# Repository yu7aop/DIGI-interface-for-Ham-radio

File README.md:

# DIGI-Interface
DIGI, PTT, CW interface, schematic, pcb, Eagle files

Project - Digi interface with 2 pots for input and output level of audio signal from PC.
Based on many different schematics, but adjusted to the needs of Radio club Zrenjanin YU7AOP.
This interface has proven to be good at working with different radio's (new and "old school":) such as:
FT901DM, FT101ZD, IC718, TS930S, FT950, FT897, some Codan's etc.

RS232 added as control port for CW and PTT. If not using CW or PTT line, simply set VOX on your RIG and use PTT via VOX on your radio.

Place interface into metal box to reduce RFI. I found on 2nd hand market defective 8 port LAN switch for about a 1$, perfect for this project.

PCB is toner-transfer method with hot Iron.
I have a lot of dual pots and PCB is adjusted for it. If you are friendly with Eagle you can change footprint for any other pot's.

Enjoy...

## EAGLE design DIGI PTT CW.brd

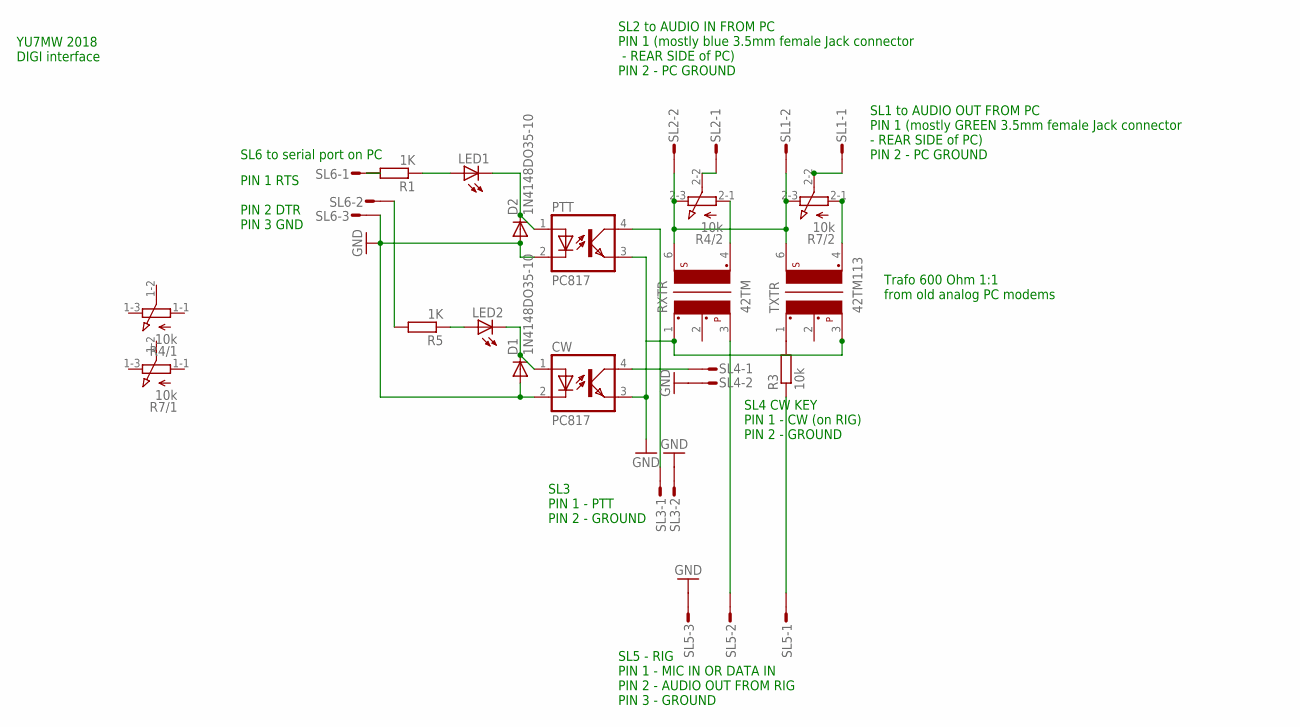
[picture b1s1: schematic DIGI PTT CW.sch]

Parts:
CW: PC817; DIL04
D1, D2: 1N4148DO35-10; DO35-10
LED1, LED2: LED3MM
PTT: PC817; DIL04
R1, R5: 1K; 0207/10
R3: 10k; 0207/10
R4, R7: 10k; 3RP/1610G
RXTR: 42TM
SL1, SL2, SL3, SL4: M02S; 02P
SL5, SL6: M03S; 03P
TXTR: 42TM113; 42TM

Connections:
GND: CW.2 (C), CW.3 (EMIT), D1.A, D2.A, PTT.2 (C), PTT.3 (EMIT), RXTR.1, SL3.2, SL4.2, SL5.3, SL6.3, TXTR.3
unnamed: LED1.A, R1.1
unnamed: R5.2, SL6.2
unnamed: CW.1 (A), D1.C, LED2.K (C)
unnamed: CW.4 (COL), SL4.1
unnamed: RXTR.3, SL5.2
unnamed: R3.1, SL5.1
unnamed: R4.2-2 (S), SL2.1
unnamed: R4.2-3 (E), R7.2-3 (E), RXTR.6, SL1.2, SL2.2, TXTR.6
unnamed: R3.2, TXTR.1
unnamed: R1.2, SL6.1
unnamed: R4.2-1 (A), RXTR.4
unnamed: R7.2-2 (S), SL1.1
unnamed: LED2.A, R5.1
unnamed: R7.2-1 (A), TXTR.4
unnamed: D2.C, LED1.K (C), PTT.1 (A)
unnamed: PTT.4 (COL), SL3.1

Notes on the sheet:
SL6 to serial port on PC
PIN 1 RTS PIN 2 DTR PIN 3 GND
SL5 - RIG PIN 1 - MIC IN OR DATA IN PIN 2 - AUDIO OUT FROM RIG PIN 3 - GROUND
SL3 PIN 1 - PTT PIN 2 - GROUND
SL4 CW KEY PIN 1 - CW (on RIG) PIN 2 - GROUND
SL2 to AUDIO IN FROM PC PIN 1 (mostly blue 3.5mm female Jack connector - REAR SIDE of PC) PIN 2 - PC GROUND
SL1 to AUDIO OUT FROM PC PIN 1 (mostly GREEN 3.5mm female Jack connector - REAR SIDE of PC) PIN 2 - PC GROUND
Trafo 600 Ohm 1:1 from old analog PC modems
YU7MW 2018 DIGI interface

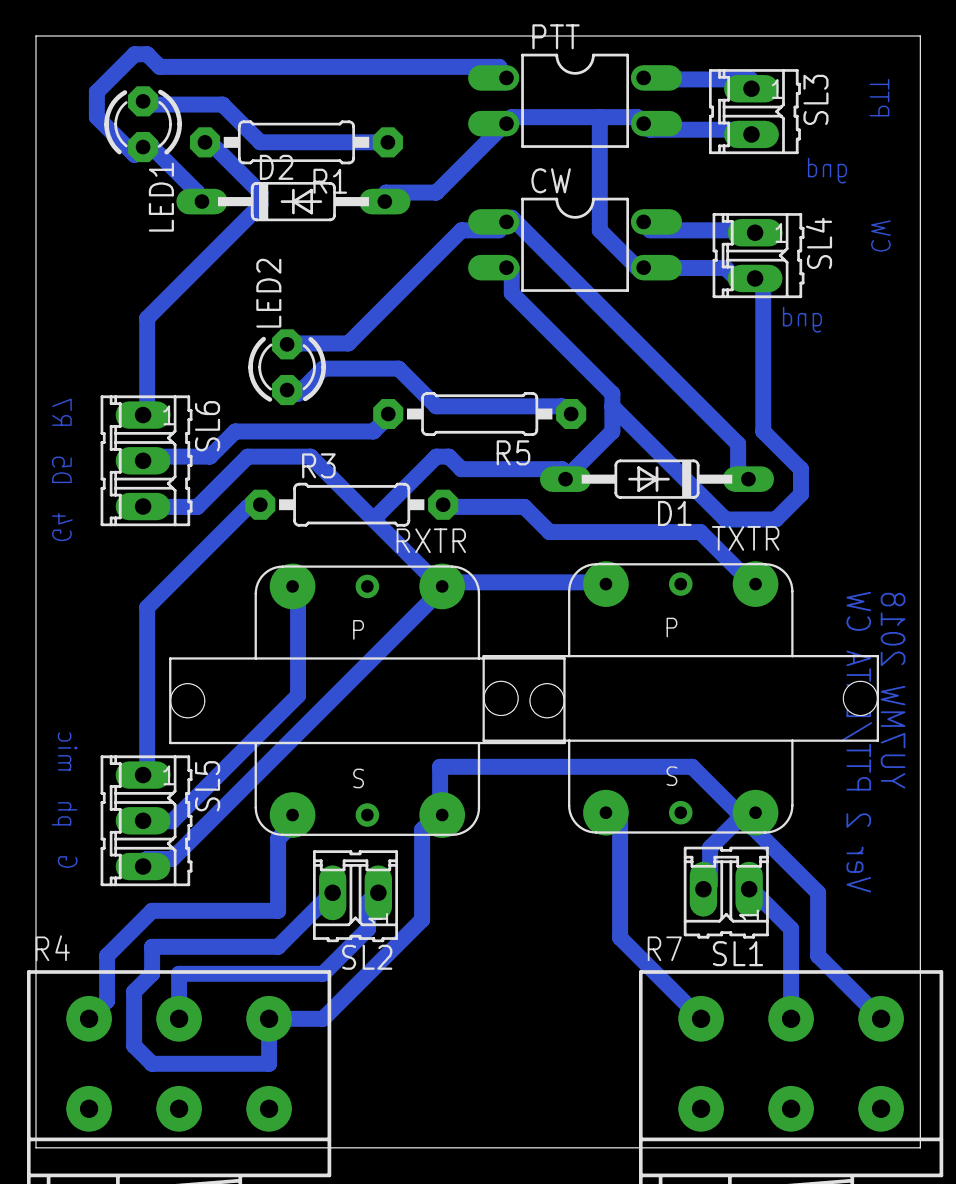
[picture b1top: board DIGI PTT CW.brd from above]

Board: 2 copper layers, 49.1 x 61.8 mm, 19 parts (0 on the bottom side), 17 nets.
